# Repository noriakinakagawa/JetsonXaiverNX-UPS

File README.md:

# JetsonXaiverNX-UPS
Jetson Xaiver NXのための、市販のRC用Li-Poバッテリを電源とするUPS装置。

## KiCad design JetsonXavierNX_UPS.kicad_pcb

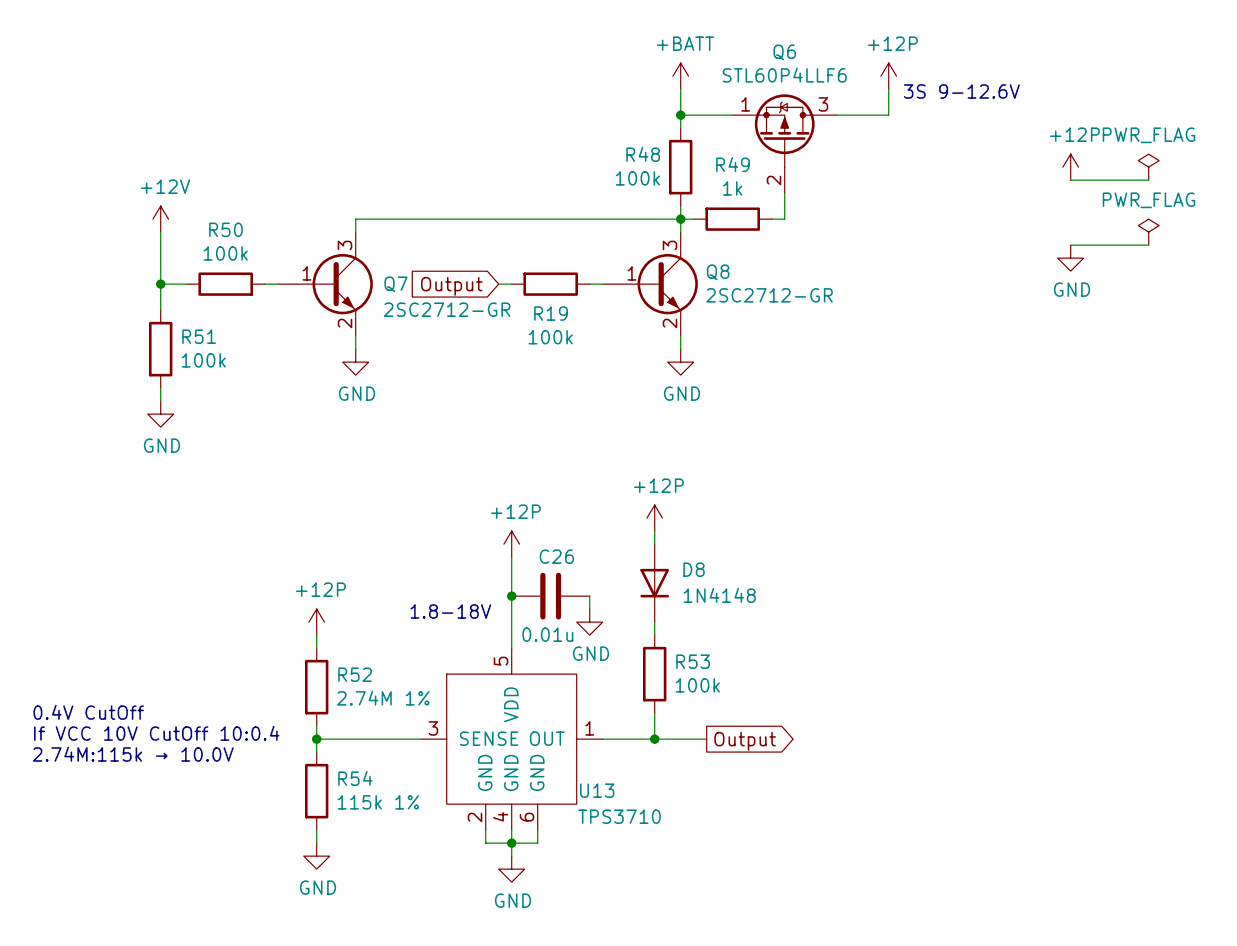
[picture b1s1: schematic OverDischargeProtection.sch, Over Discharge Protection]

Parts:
C26: 0.01u; C_0603
D8: 1N4148; D_SOD-123
Q6: STL60P4LLF6; 8-PowerVDFN
Q7, Q8: 2SC2712-GR; SC-59
R19, R48, R50, R51, R53: 100k; R_0603
R49: 1k; R_0603
R52: 2.74M 1%; R_0603
R54: 115k 1%; R_0603
U13: TPS3710; TSOT-23-6

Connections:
+12P: C26.1, D8.2 (A), Q6.3 (D), R52.1, U13.5 (VDD); also elsewhere on the board
+12V: R50.1, R51.1; also elsewhere on the board
+BATT: Q6.1 (S), R48.1; also elsewhere on the board
GND: C26.2, Q7.2 (E), Q8.2 (E), R51.2, R54.2, U13.2 (GND), U13.4 (GND), U13.6 (GND); also elsewhere on the board
unnamed: D8.1 (K), R53.1
unnamed: Q6.2 (G), R49.1
unnamed: Q7.1 (B), R50.2
unnamed: Q7.3 (C), Q8.3 (C), R48.2, R49.2
unnamed: Q8.1 (B), R19.1
unnamed: R52.2, R54.1, U13.3 (SENSE)
Output: R19.2, R53.2, U13.1 (OUT)

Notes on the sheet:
1.8-18V
3S 9-12.6V
0.4V CutOff If VCC 10V CutOff 10:0.4 2.74M:115k → 10.0V

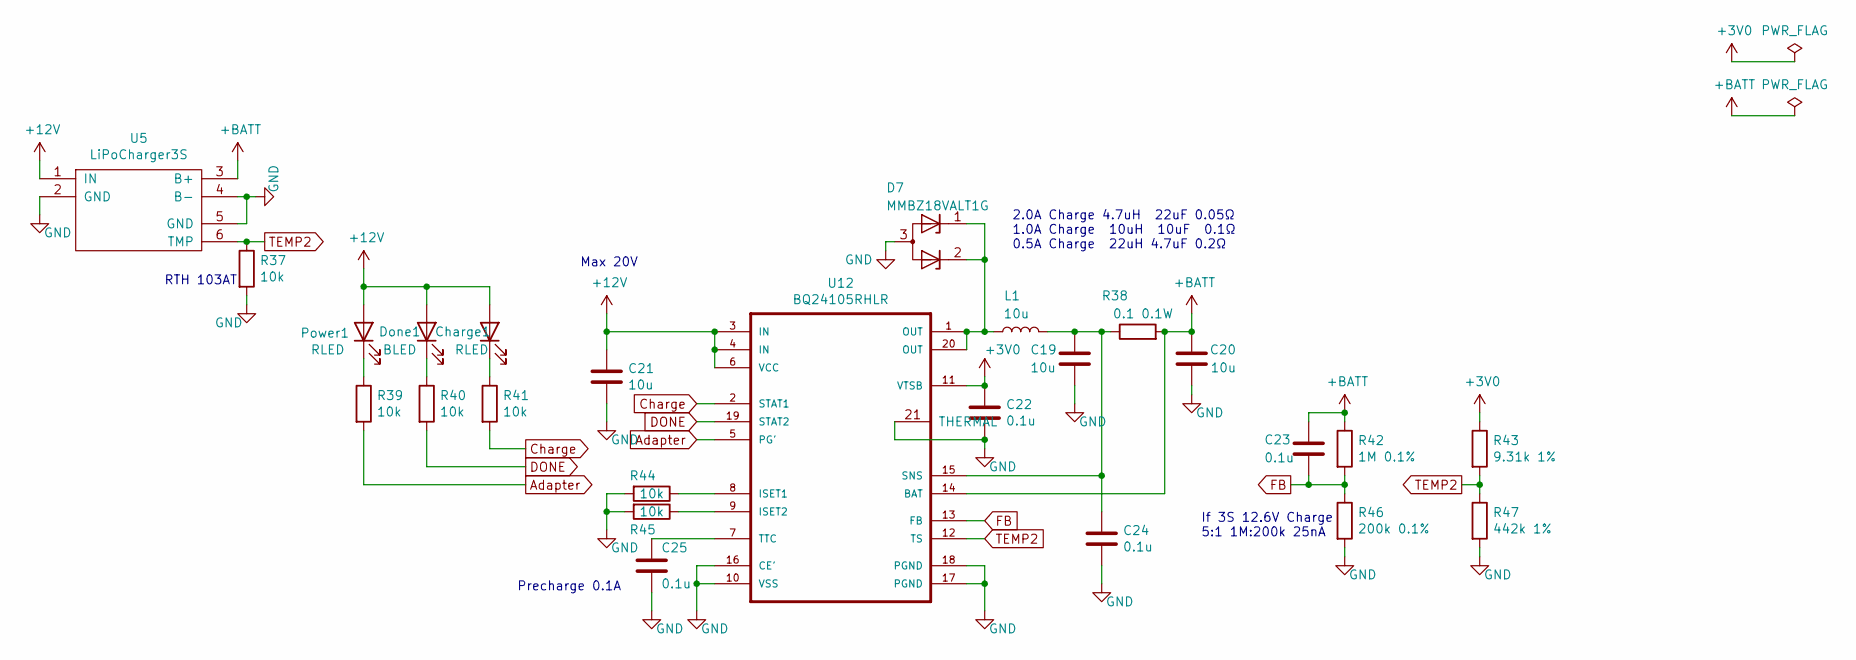
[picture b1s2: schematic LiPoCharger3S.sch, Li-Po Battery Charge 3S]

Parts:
C19, C20, C21: 10u; C_0805
C22, C23, C24, C25: 0.1u; C_0603
Charge1: RLED; LED_0603
D7: MMBZ18VALT1G; SOT-23
Done1: BLED; LED_0603
L1: 10u; Inductor_Taiyo-Yuden_NR-50xx
Power1: RLED; LED_0603
R37, R39, R40, R41, R44, R45: 10k; R_0603
R38: 0.1 0.1W; R_1206
R42: 1M 0.1%; R_0603
R43: 9.31k 1%; R_0603
R46: 200k 0.1%; R_0603
R47: 442k 1%; R_0603
U5: LiPoCharger3S
U12: BQ24105RHLR; IC_MSP430FR2522IRHLR

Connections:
+3V0: C22.1, R43.1, U12.11 (VTSB)
+12V: C21.1, Charge1.2 (A), Done1.2 (A), Power1.2 (A), U5.1 (IN), U12.3 (IN), U12.4 (IN), U12.6 (VCC); also elsewhere on the board
+BATT: C20.1, C23.1, R38.2, R42.1, U5.3 (B+), U12.14 (BAT); also elsewhere on the board
Adapter: R39.2, U12.5 (PG')
Charge: R41.2, U12.2 (STAT1)
DONE: R40.2, U12.19 (STAT2)
FB: C23.2, R42.2, R46.1, U12.13 (FB)
GND: C19.2, C20.2, C21.2, C22.2, C24.2, C25.2, D7.3 (A), R37.2, R44.2, R45.2, R46.2, R47.2, U5.2 (GND), U5.4 (B-), U5.5 (GND), U12.10 (VSS), U12.16 (CE'), U12.17 (PGND), U12.18 (PGND), U12.21 (THERMAL); also elsewhere on the board
unnamed: C19.1, C24.1, L1.2, R38.1, U12.15 (SNS)
unnamed: C25.1, U12.7 (TTC)
unnamed: Charge1.1 (K), R41.1
unnamed: D7.1 (K), D7.2 (K), L1.1, U12.1 (OUT), U12.20 (OUT)
unnamed: Done1.1 (K), R40.1
unnamed: Power1.1 (K), R39.1
unnamed: R44.1, U12.8 (ISET1)
unnamed: R45.1, U12.9 (ISET2)
TEMP2: R37.1, R43.2, R47.1, U5.6 (TMP), U12.12 (TS)

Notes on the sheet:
If 3S 12.6V Charge 5:1 1M:200k 25nA
Precharge 0.1A
2.0A Charge 4.7uH 22uF 0.05Ω 1.0A Charge 10uH 10uF 0.1Ω 0.5A Charge 22uH 4.7uF 0.2Ω
Max 20V
RTH 103AT

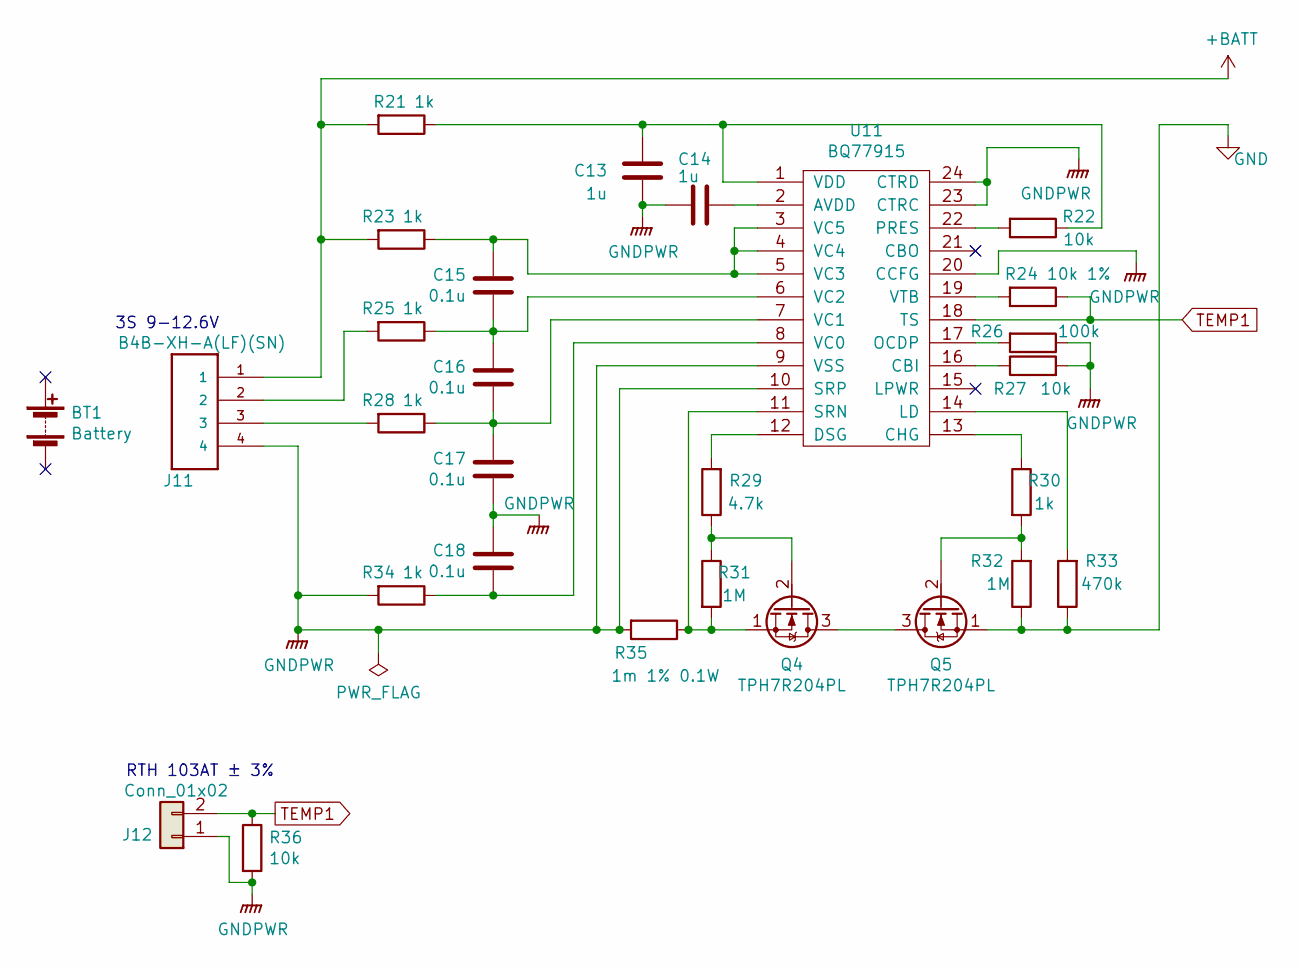
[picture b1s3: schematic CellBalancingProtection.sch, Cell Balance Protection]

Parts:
BT1: Battery; LiPo3S1000mAh
C13, C14: 1u; C_0603
C15, C16, C17, C18: 0.1u; C_0603
J11: B4B-XH-A(LF)(SN); JST_XH_B04B-XH-A_04x2.50mm_Straight
J12: Conn_01x02; Pin_Header_Straight_1x02_Pitch2.00mm
Q4, Q5: TPH7R204PL; 8-PowerVDFN
R21, R23, R25, R28, R30, R34: 1k; R_0603
R22, R27, R36: 10k; R_0603
R24: 10k 1%; R_0603
R26: 100k; R_0603
R29: 4.7k; R_0603
R31, R32: 1M; R_0603
R33: 470k; R_0603
R35: 1m 1% 0.1W; R_1206
U11: BQ77915; TSSOP-24_4.4x7.8mm_Pitch0.65mm

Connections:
+BATT: J11.1, R21.2, R23.2; also elsewhere on the board
GND: Q5.1 (S), R32.1, R33.1; also elsewhere on the board
GNDPWR: C13.1, C14.2, C17.2, C18.1, J11.4, J12.1, R26.1, R27.2, R34.2, R35.2, R36.2, U11.9 (VSS), U11.10 (SRP), U11.20 (CCFG), U11.23 (CTRC), U11.24 (CTRD); also elsewhere on the board
unnamed: C13.2, R21.1, R22.1, U11.1 (VDD)
unnamed: C14.1, U11.2 (AVDD)
unnamed: C15.1, R23.1, U11.3 (VC5), U11.4 (VC4), U11.5 (VC3)
unnamed: C15.2, C16.1, R25.1, U11.6 (VC2)
unnamed: C16.2, C17.1, R28.1, U11.7 (VC1)
unnamed: C18.2, R34.1, U11.8 (VC0)
unnamed 37: J11.2, R25.2; also elsewhere on the board
unnamed 38: J11.3, R28.2; also elsewhere on the board
unnamed: Q4.1 (S), R31.2, R35.1, U11.11 (SRN)
unnamed: Q4.2 (G), R29.1, R31.1
unnamed: Q4.3 (D), Q5.3 (D)
unnamed: Q5.2 (G), R30.2, R32.2
unnamed: R22.2, U11.22 (PRES)
unnamed: R24.2, U11.19 (VTB)
unnamed: R26.2, U11.17 (OCDP)
unnamed: R27.1, U11.16 (CBI)
unnamed: R29.2, U11.12 (DSG)
unnamed: R30.1, U11.13 (CHG)
unnamed: R33.2, U11.14 (LD)
TEMP1: J12.2, R24.1, R36.1, U11.18 (TS)

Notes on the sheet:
3S 9-12.6V
RTH 103AT ± 3%

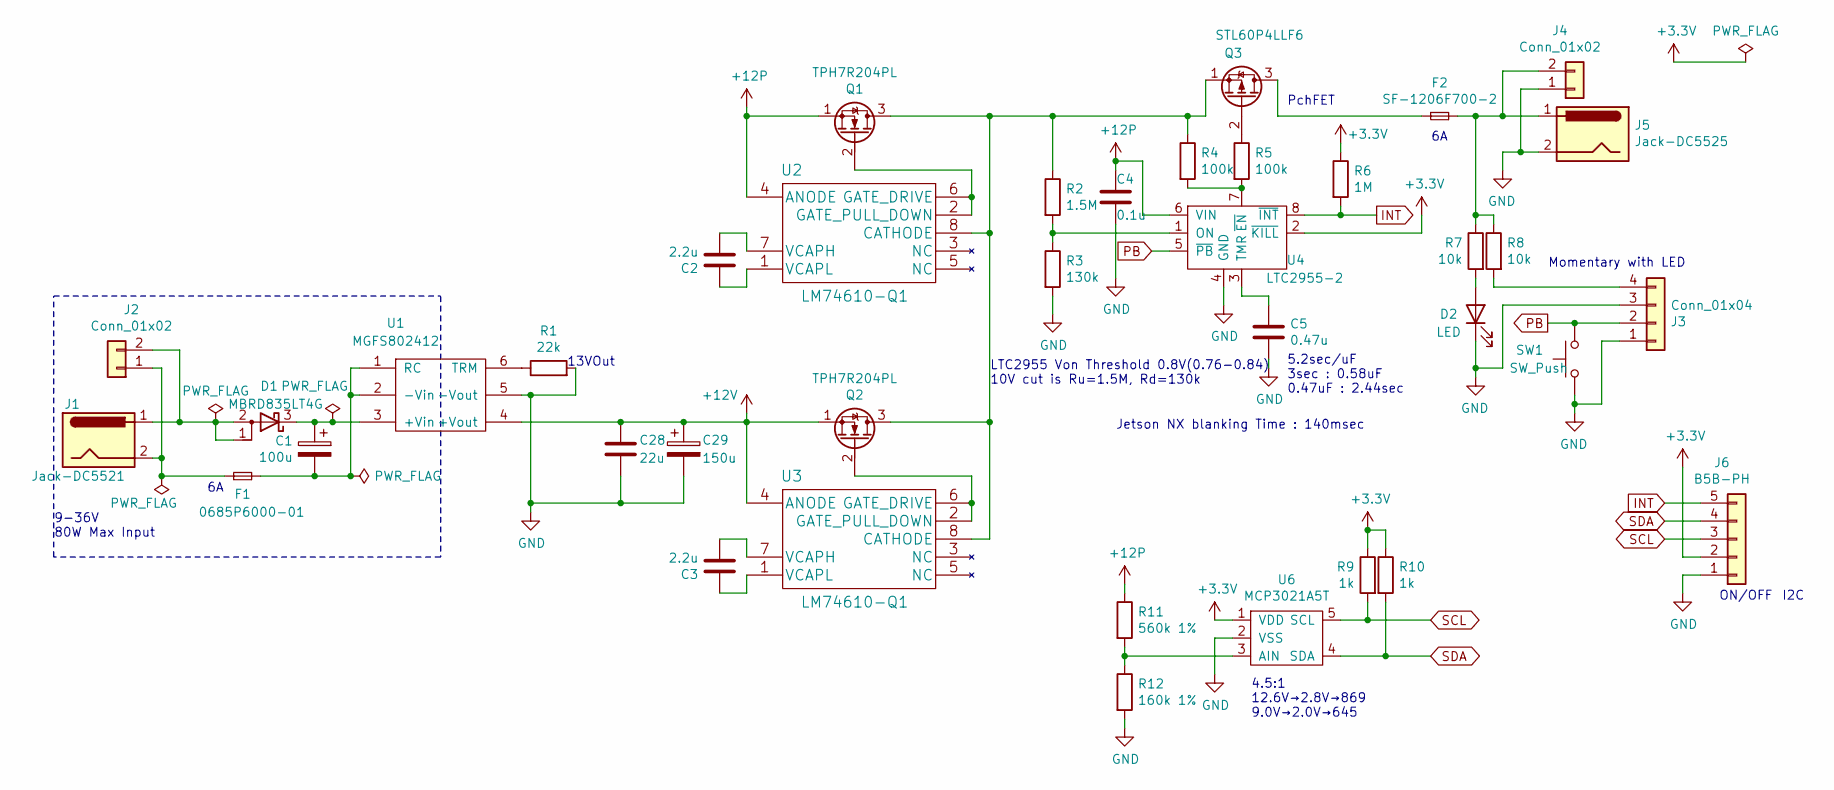
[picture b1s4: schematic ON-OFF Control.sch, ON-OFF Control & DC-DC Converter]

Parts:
C1: 100u; EEE-1VA101XP
C2, C3: 2.2u; C_0603
C4: 0.1u; C_0603
C5: 0.47u; C_0603
C28: 22u; C_1210
C29: 150u; PCR1V151MCL1GS
D1: MBRD835LT4G; TO-252-3
D2: LED; LED_0603
F1: 0685P6000-01; Fuse_SMD1206_HandSoldering
F2: SF-1206F700-2; Fuse_SMD1206_HandSoldering
J1: Jack-DC5521; CUI_PJ-002B
J2, J4: Conn_01x02; JST_XH_B02B-XH-A_02x2.50mm_Straight
J3: Conn_01x04; JST_PH_B4B-PH-K_04x2.00mm_Straight
J5: Jack-DC5525; CUI_PJ-002B
J6: B5B-PH; JST_PH_B5B-PH-K_05x2.00mm_Straight
Q1, Q2: TPH7R204PL; 8-PowerVDFN
Q3: STL60P4LLF6; 8-PowerVDFN
R1: 22k; R_0603
R2: 1.5M; R_0603
R3: 130k; R_0603
R4, R5: 100k; R_0603
R6: 1M; R_0603
R7, R8: 10k; R_0603
R9, R10: 1k; R_0603
R11: 560k 1%; R_0603
R12: 160k 1%; R_0603
SW1: SW_Push; SW_Tactile_SPST_Angled_PTS645Vx83-2LFS
U1: MGFS802412; MGFS80
U2, U3: LM74610-Q1; 8-VSSOP
U4: LTC2955-2; TSOT-23-8
U6: MCP3021A5T; SOT-23-5

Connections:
+3V3: J6.2, R6.1, R9.1, R10.1, U4.2 (~KILL), U6.1 (VDD)
+12P: C4.1, Q1.1 (S), R11.1, U2.4 (ANODE), U4.6 (VIN); also elsewhere on the board
+12V: C28.1, C29.1, Q2.1 (S), U1.4 (+Vout), U3.4 (ANODE); also elsewhere on the board
GND: C4.2, C5.2, C28.2, C29.2, D2.1 (K), J3.1, J3.3, J4.1, J5.2, J6.1, R1.2, R3.2, R12.2, SW1.1, U1.5 (-Vout), U4.4 (GND), U6.2 (VSS); also elsewhere on the board
INT: J6.5, R6.2, U4.8 (~INT)
unnamed: C1.1, D1.3 (K), U1.3 (+Vin)
unnamed: C1.2, F1.2, U1.1 (RC), U1.2 (-Vin)
unnamed: C2.1, U2.1 (VCAPL)
unnamed: C2.2, U2.7 (VCAPH)
unnamed: C3.1, U3.1 (VCAPL)
unnamed: C3.2, U3.7 (VCAPH)
unnamed: C5.1, U4.3 (TMR)
unnamed: D1.1 (A), D1.2 (A), J1.1, J2.2
unnamed: D2.2 (A), R7.2
unnamed: F1.1, J1.2, J2.1
unnamed: F2.1, Q3.3 (D)
unnamed: F2.2, J4.2, J5.1, R7.1, R8.1
unnamed: J3.4, R8.2
unnamed: Q1.2 (G), U2.2 (GATE_PULL_DOWN), U2.6 (GATE_DRIVE)
unnamed: Q1.3 (D), Q2.3 (D), Q3.1 (S), R2.1, R4.1, U2.8 (CATHODE), U3.8 (CATHODE)
unnamed: Q2.2 (G), U3.2 (GATE_PULL_DOWN), U3.6 (GATE_DRIVE)
unnamed: Q3.2 (G), R5.1
unnamed: R1.1, U1.6 (TRM)
unnamed: R2.2, R3.1, U4.1 (ON)
unnamed: R4.2, R5.2, U4.7 (~EN)
unnamed: R11.2, R12.1, U6.3 (AIN)
PB: J3.2, SW1.2, U4.5 (~PB)
SCL: J6.3, R9.2, U6.5 (SCL)
SDA: J6.4, R10.2, U6.4 (SDA)

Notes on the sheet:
PchFET
ON/OFF
I2C
4.5:1 12.6V→2.8V→869 9.0V→2.0V→645
13VOut
Jetson NX blanking Time : 140msec
9-36V 80W Max Input
Momentary with LED
5.2sec/uF 3sec : 0.58uF 0.47uF : 2.44sec
LTC2955 Von Threshold 0.8V(0.76-0.84) 10V cut is Ru=1.5M, Rd=130k

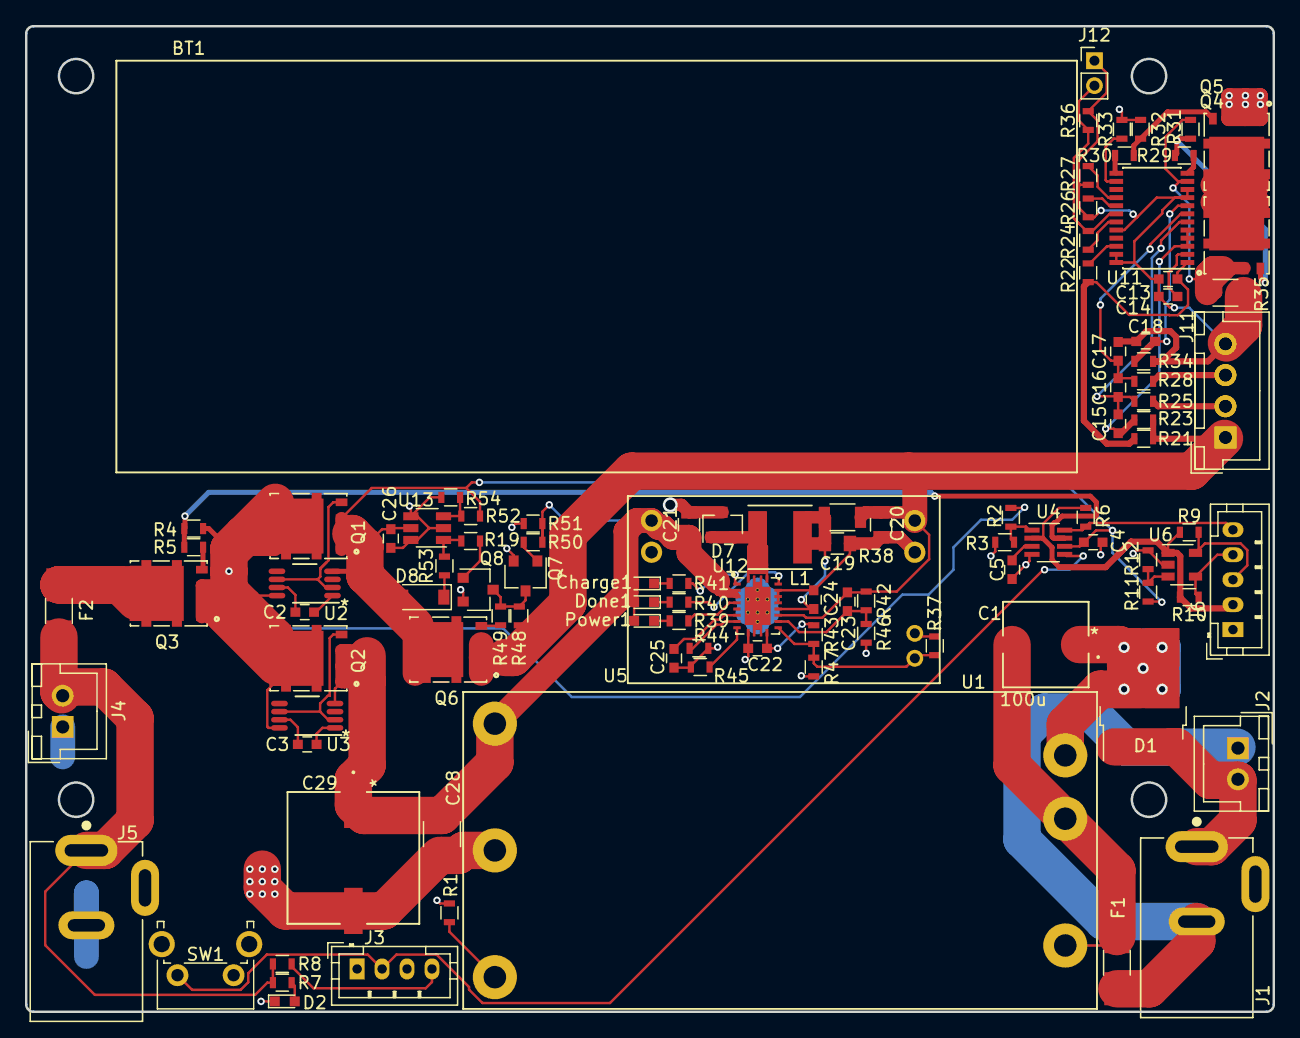
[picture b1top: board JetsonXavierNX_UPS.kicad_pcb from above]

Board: 2 copper layers, 100.0 x 79.0 mm, 106 parts (1 on the bottom side), 72 nets.

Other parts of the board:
J11#2: B4B-XH-A(LF)(SN); JST_XH_B04B-XH-A_04x2.50mm_Straight

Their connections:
+BATT: J11#2.1; also elsewhere on the board
GNDPWR: J11#2.4; also elsewhere on the board
unnamed 37: J11#2.2; also elsewhere on the board
unnamed 38: J11#2.3; also elsewhere on the board

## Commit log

2021-01-03 First Comitt
